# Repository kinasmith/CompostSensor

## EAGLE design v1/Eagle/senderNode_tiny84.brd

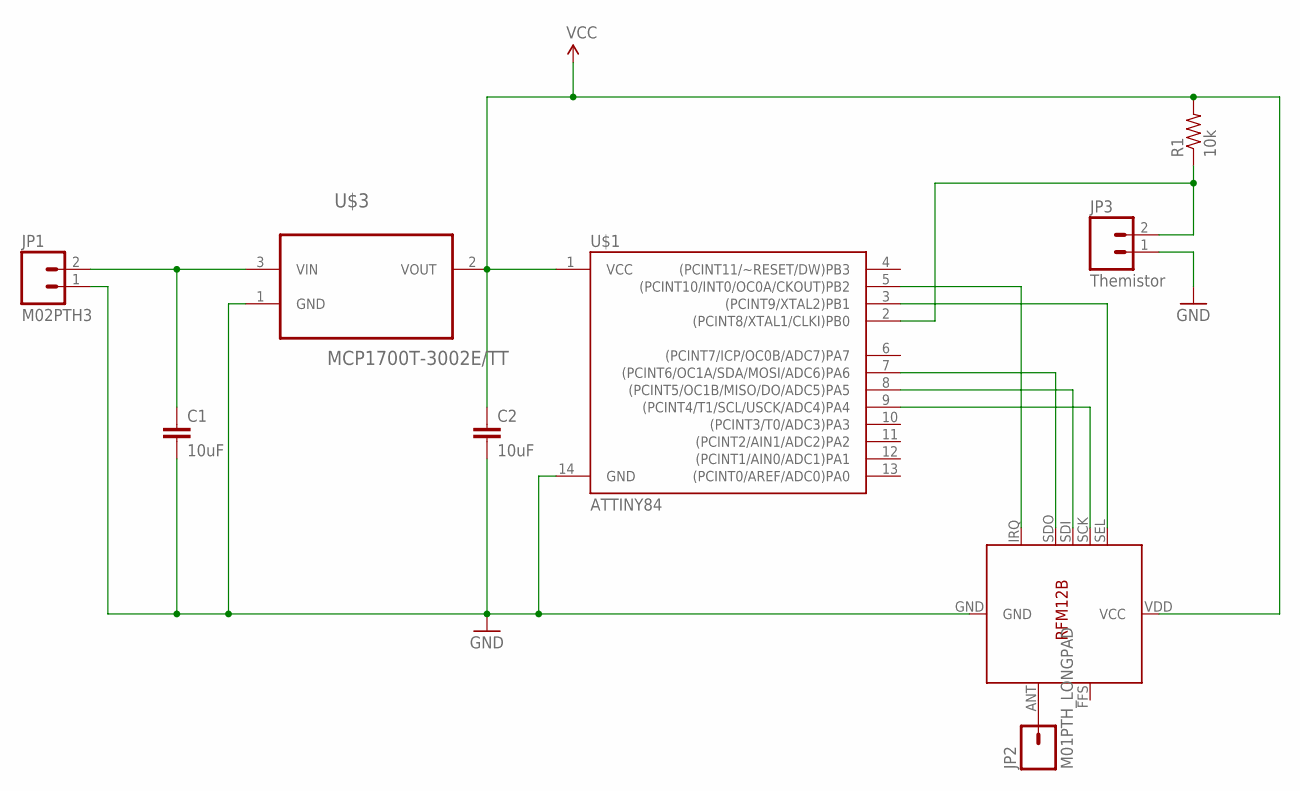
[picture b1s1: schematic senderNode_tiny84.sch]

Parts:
C1, C2: 10uF; 0603-CAP
JP1: M02PTH3; 1X02_LONGPADS
JP2: M01PTH_LONGPAD; 1X01_LONGPAD
JP3: Themistor; 1X02_LONGPADS
R1: 10k; 0805
U$1: ATTINY84; SO14
U$2: RFM12B
U$3: MCP1700T-3002E/TT; SOT95P237X112-3N

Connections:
GND: C1.2, C2.2, JP1.1, JP3.1, U$1.14 (GND), U$2.GND, U$3.1 (GND)
unnamed: U$1.5 ((PCINT10/INT0/OC0A/CKOUT)PB2), U$2.IRQ
unnamed: U$1.7 ((PCINT6/OC1A/SDA/MOSI/ADC6)PA6), U$2.SDO
unnamed: U$1.8 ((PCINT5/OC1B/MISO/DO/ADC5)PA5), U$2.SDI
unnamed: U$1.9 ((PCINT4/T1/SCL/USCK/ADC4)PA4), U$2.SCK
unnamed: U$1.3 ((PCINT9/XTAL2)PB1), U$2.SEL
unnamed: C1.1, JP1.2, U$3.3 (VIN)
unnamed: JP3.2, R1.1, U$1.2 ((PCINT8/XTAL1/CLKI)PB0)
unnamed: JP2.1, U$2.ANT
VCC: C2.1, R1.2, U$1.1 (VCC), U$2.VDD (VCC), U$3.2 (VOUT)

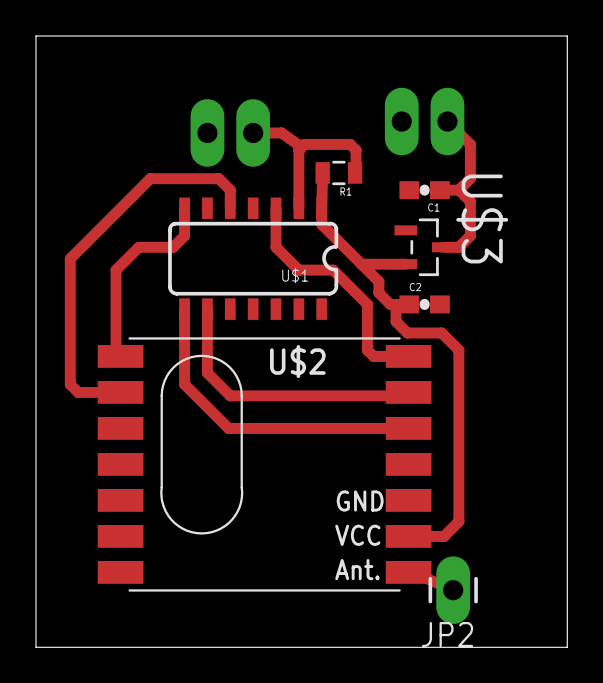
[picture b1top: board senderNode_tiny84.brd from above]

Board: 2 copper layers, 29.5 x 34.0 mm, 9 parts (0 on the bottom side), 10 nets.

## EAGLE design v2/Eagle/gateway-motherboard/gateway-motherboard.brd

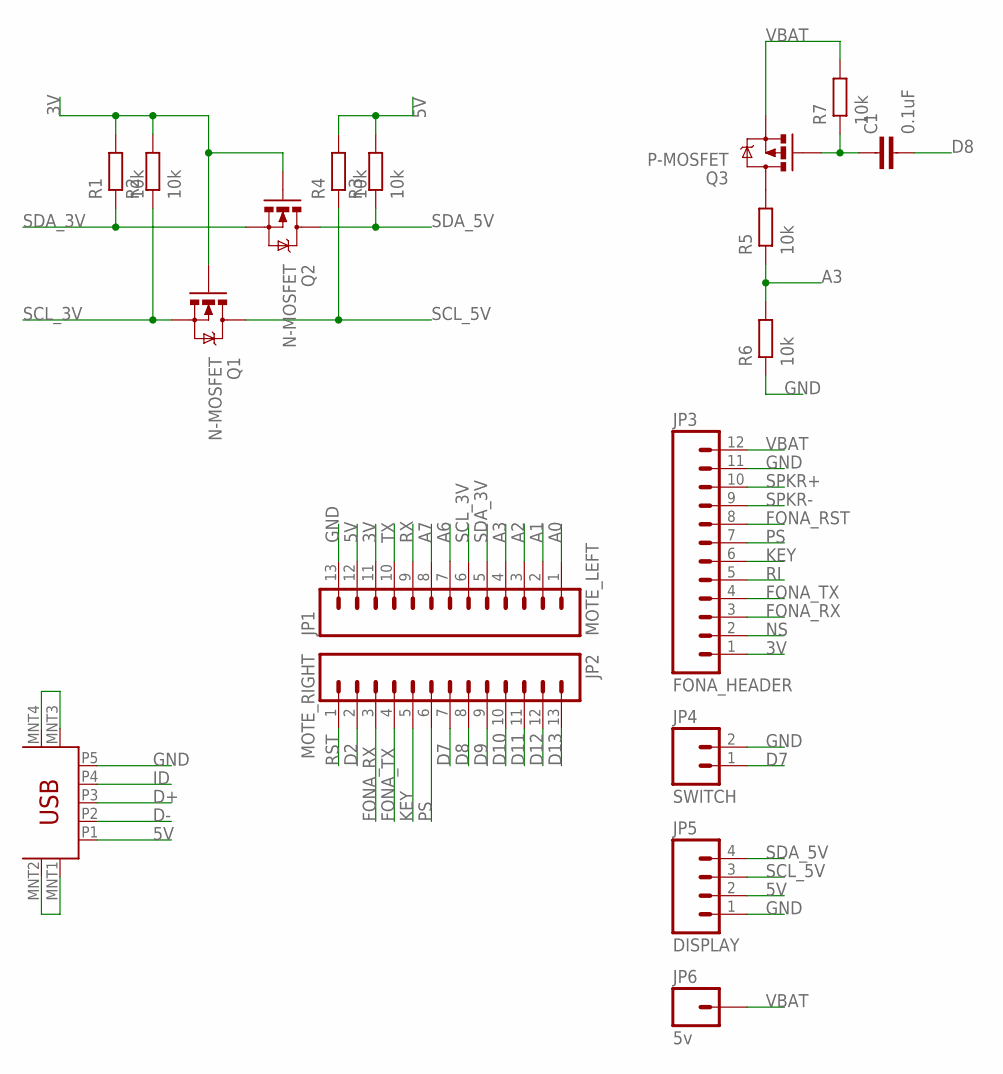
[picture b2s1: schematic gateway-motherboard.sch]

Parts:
C1: 0.1uF; C0603-L
JP1: MOTE_LEFT; 1X13-LONGPADS
JP2: MOTE_RIGHT; 1X13-LONGPADS
JP3: FONA_HEADER; 1X12_LONGPADS
JP4: SWITCH; 1X02_LOCK_LONGPADS
JP5: DISPLAY; 1X04_LONGPADS
JP6: 5v; 1X01NS-KIT
Q1, Q2: N-MOSFET; SOT23
Q3: P-MOSFET; SOT23-3
R1, R2, R3, R4, R5, R6, R7: 10k; R0603-L
U$1: USB-MINIB; USB-MINIB_HOLE_RETENTION

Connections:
3V: JP1.11, JP3.1, Q1.1 (G), Q2.1 (G), R1.2, R2.2
5V: JP1.12, JP5.2, R3.2, R4.2, U$1.P1 (VBUS)
A0: JP1.1
A1: JP1.2
A2: JP1.3
A3: JP1.4, R5.1, R6.2
A6: JP1.7
A7: JP1.8
D2: JP2.2
D7: JP2.7, JP4.1
D8: C1.2, JP2.8
D9: JP2.9
D10: JP2.10
D11: JP2.11
D12: JP2.12
D13: JP2.13
D+: U$1.P3 (D+)
D-: U$1.P2 (D-)
FONA_RST: JP3.8
FONA_RX: JP2.3, JP3.3
FONA_TX: JP2.4, JP3.4
GND: JP1.13, JP3.11, JP4.2, JP5.1, R6.1, U$1.MNT1 (MTN1), U$1.MNT2 (MTN2), U$1.MNT3 (MTN3), U$1.MNT4 (MTN4), U$1.P5 (GND)
ID: U$1.P4 (ID)
KEY: JP2.5, JP3.6
unnamed: Q3.3 (D), R5.2
unnamed: C1.1, Q3.1 (G), R7.1
NS: JP3.2
PS: JP2.6, JP3.7
RI: JP3.5
RST: JP2.1
RX: JP1.9
SCL_3V: JP1.6, Q1.2 (S), R2.1
SCL_5V: JP5.3, Q1.3 (D), R4.1
SDA_3V: JP1.5, Q2.2 (S), R1.1
SDA_5V: JP5.4, Q2.3 (D), R3.1
SPKR+: JP3.10
SPKR-: JP3.9
TX: JP1.10
VBAT: JP3.12, JP6.1, Q3.2 (S), R7.2

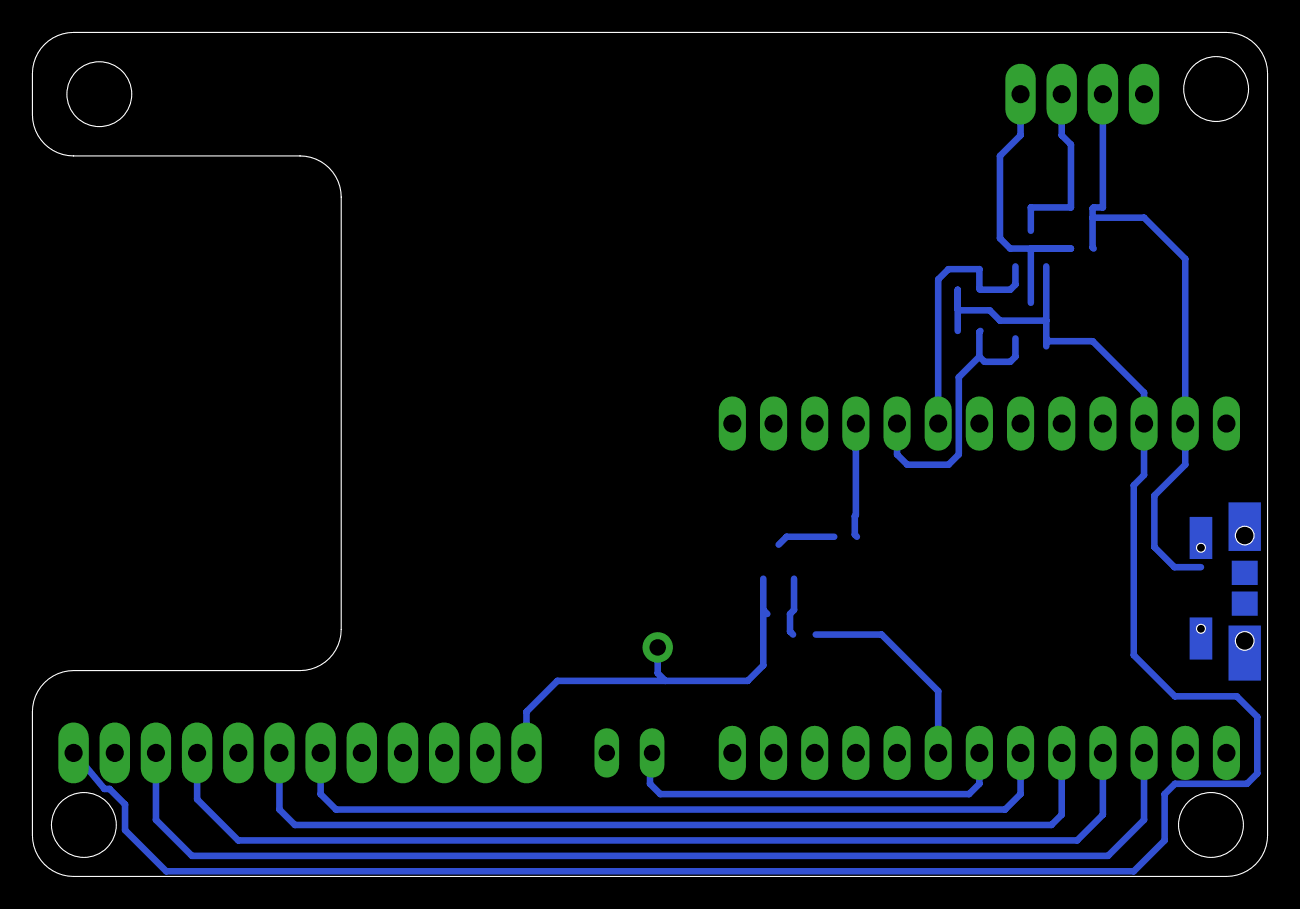
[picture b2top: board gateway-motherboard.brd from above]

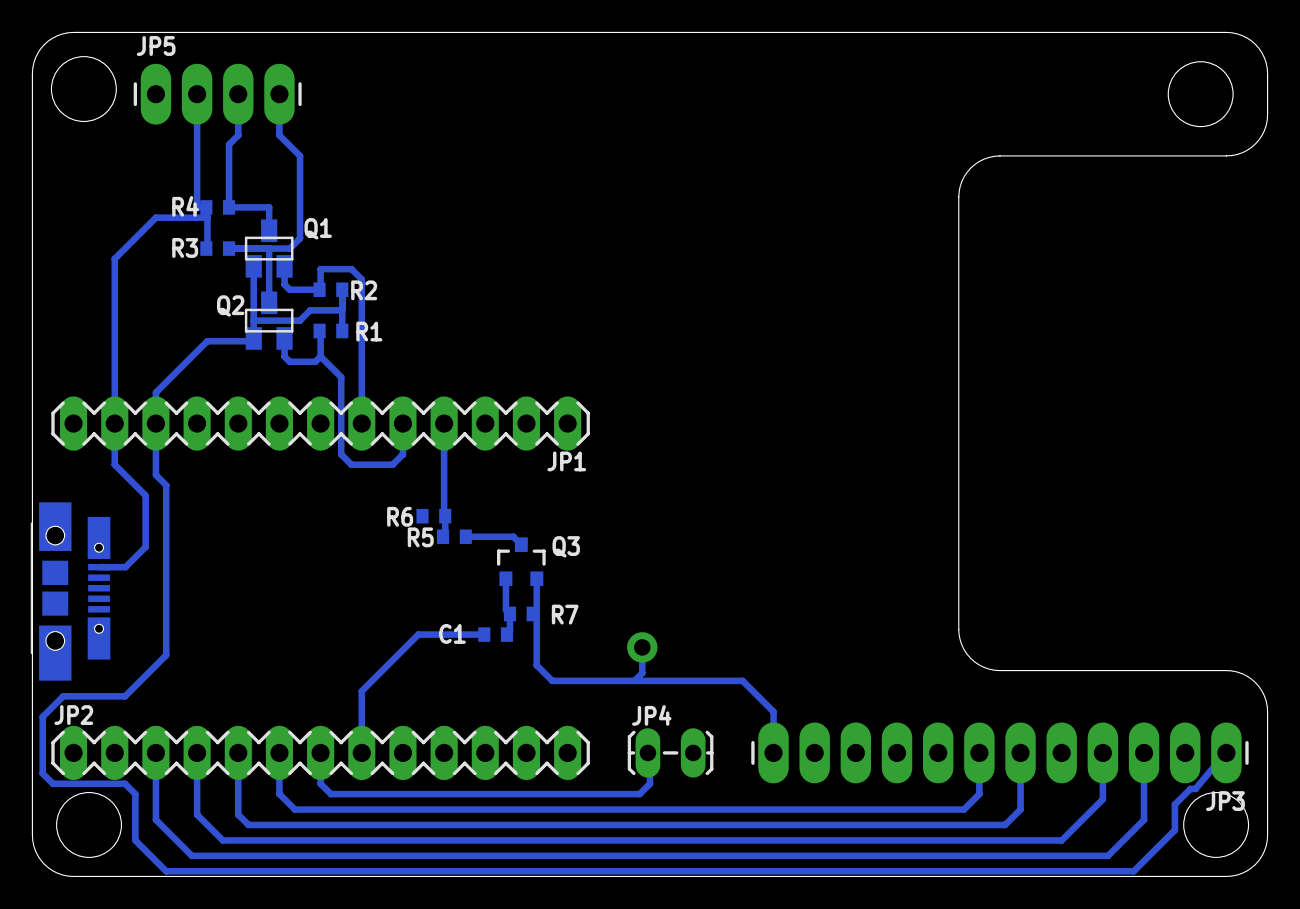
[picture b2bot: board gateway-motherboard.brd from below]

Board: 2 copper layers, 76.2 x 52.1 mm, 18 parts (18 on the bottom side), 17 nets.

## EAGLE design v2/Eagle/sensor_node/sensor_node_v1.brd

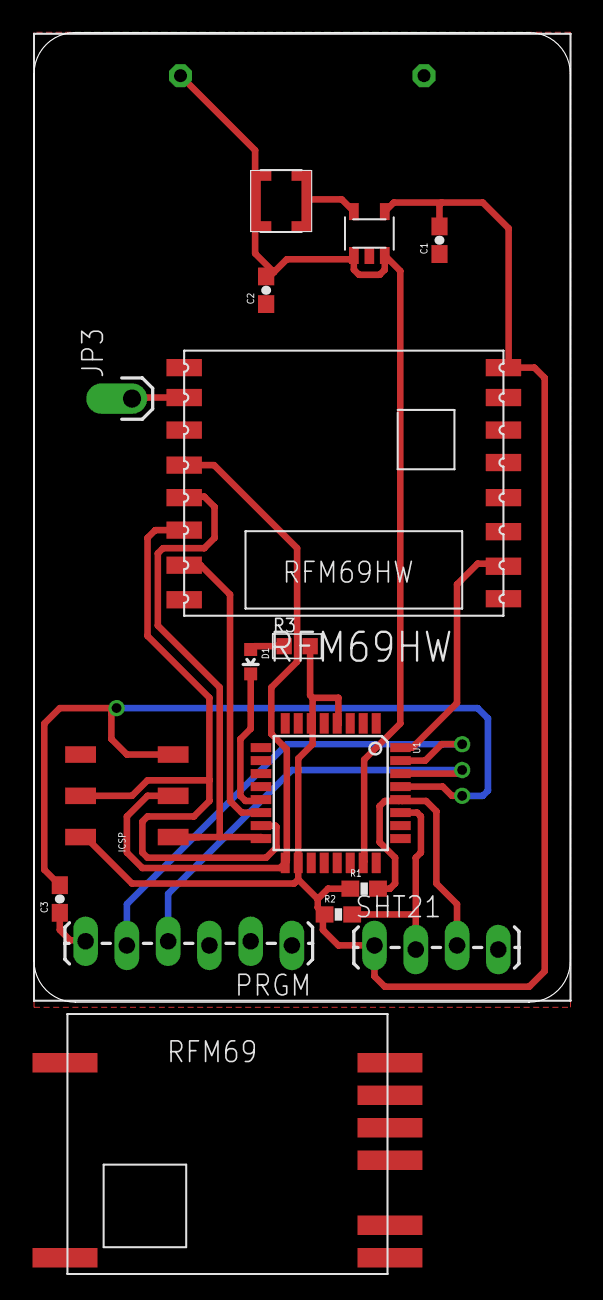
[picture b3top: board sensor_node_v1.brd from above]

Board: 2 copper layers, 33.0 x 59.7 mm, 17 parts (0 on the bottom side), 18 nets.

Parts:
C1, C2: 10uF; 0603-CAP
C3: 0.1uF; 0603-CAP
D1: BLUE; LED-0603
ICSP: 2X3_SMD
JP3: M01OFFSET; 1X01_OFFSET
PRGM: 1X06_LOCK_LONGPADS
R1, R2: 10k; 0603-RES
R3: R0603-N
RFM69HW: RFM69HW; RFM
SHT21: 1X04_LOCK_LONGPADS
U1: ATMEGA328P; TQFP32-08
U$1: KEYSTONEAAHOLDER_2CELL
U$2: TPS61097-33; SOT23-5
U$3: COILCRAFT_DO3314
U$4: RFM69HW_MIN; RFM69

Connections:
ANT: JP3.1, RFM69HW.ANT
GND: C1.1, C2.1, ICSP.6, PRGM.1, RFM69HW.GNDB, SHT21.4, U1.3, U1.5, U1.21, U$1.P$2, U$2.P$2
IRQ: RFM69HW.DIO0, U1.32
LED: D1.C, U1.13
MISO: ICSP.1, RFM69HW.MISO, U1.16
MOSI: ICSP.4, RFM69HW.MOSI, U1.15
unnamed: U$2.P$5, U$3.P$1
unnamed: C3.1, PRGM.6
unnamed: D1.A, R3.1
RST: C3.2, ICSP.5, U1.29
RX: PRGM.4, U1.30
SCK: ICSP.3, RFM69HW.SCK, U1.17
SCL: R1.2, SHT21.3, U1.28
SDA: R2.2, SHT21.2, U1.27
SS: RFM69HW.NSS, U1.14
TX: PRGM.5, U1.31
VBAT: C2.2, U1.23, U$1.P$1, U$2.P$1, U$2.P$3, U$3.P$2
VCC: C1.2, ICSP.2, R1.1, R2.1, R3.2, RFM69HW.VCC, SHT21.1, U1.4, U1.6, U1.18, U$2.P$4

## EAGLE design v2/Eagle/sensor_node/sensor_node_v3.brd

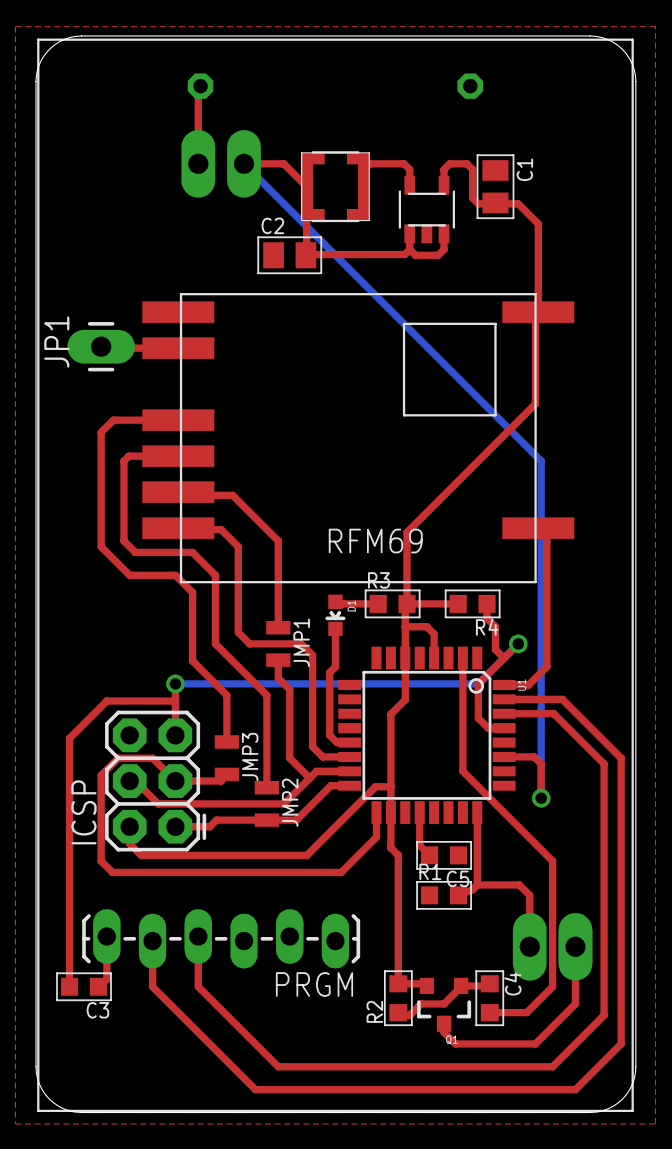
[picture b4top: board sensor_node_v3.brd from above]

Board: 2 copper layers, 33.3 x 59.8 mm, 24 parts (0 on the bottom side), 25 nets.

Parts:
C1, C2: 10uF; C0805-N
C3, C4, C5: 0.1uF; C0603-N
D1: BLUE; LED-0603
ICSP: 2X3
JMP1, JMP2: 0; R0805-L
JMP3: o; R0805-L
JP1: M01PTH_LONGPAD; 1X01_LONGPAD
JP2: THERM; 1X02_LONGPADS
JP3: PWR_SW; 1X02_LONGPADS
PRGM: 1X06_LOCK_LONGPADS
Q1: MOSFET-PCHANNELSMD; SOT23-3
R1, R2, R4: 10k; R0603-N
R3: R0603-N
U1: ATMEGA328P; TQFP32-08
U$1: KEYSTONEAAHOLDER_2CELL
U$2: TPS61097-33; SOT23-5
U$3: COILCRAFT_DO3314
U$4: RFM69HW_MIN; RFM69

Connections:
ANT: JP1.1, U$4.ANA
GND: C1.1, C2.1, C5.1, ICSP.6, PRGM.1, R1.1, U1.3, U1.5, U1.21, U$1.P$2, U$2.P$2, U$4.GND
IRQ: U1.32, U$4.DIO0
LED: D1.C, U1.13
MISO: ICSP.1, JMP2.2, U1.16
MOSI: ICSP.4, JMP1.2, U1.15
unnamed: U$2.P$5, U$3.P$1
unnamed: C3.1, PRGM.6
unnamed: D1.A, R3.1
unnamed: JMP1.1, U$4.MOSI
unnamed: JMP2.1, U$4.MISO
unnamed: JMP3.1, U$4.SCK
unnamed: JP3.1, U$1.P$1
unnamed: C4.1, Q1.1, R2.1
unnamed: C5.2, U1.20
unnamed: JP2.2, Q1.3
RST: C3.2, ICSP.5, R4.1, U1.29
RX: PRGM.4, U1.30
SCK: ICSP.3, JMP3.2, U1.17
SS: U1.14, U$4.NSS
THERM: JP2.1, R1.2, U1.24
THERM_EN: C4.2, U1.2
TX: PRGM.5, U1.31
VBAT: C2.2, JP3.2, U1.27, U$2.P$1, U$2.P$3, U$3.P$2
VCC: C1.2, ICSP.2, Q1.2, R2.2, R3.2, R4.2, U1.4, U1.6, U1.18, U$2.P$4, U$4.VCC

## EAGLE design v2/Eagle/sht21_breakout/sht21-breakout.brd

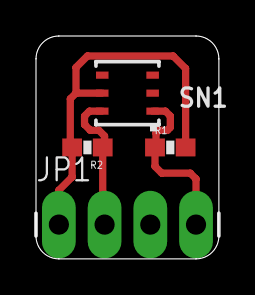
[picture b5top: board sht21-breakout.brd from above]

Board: 2 copper layers, 10.2 x 12.4 mm, 4 parts (0 on the bottom side), 4 nets.

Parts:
JP1: 1X04_LONGPADS
R1, R2: 10k; 0603-RES
SN1: SHT21; DFN6/SHT

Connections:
GND: JP1.3, SN1.2
SCL: JP1.2, R2.1, SN1.6
SDA: JP1.4, R1.1, SN1.1
VCC: JP1.1, R1.2, R2.2, SN1.5

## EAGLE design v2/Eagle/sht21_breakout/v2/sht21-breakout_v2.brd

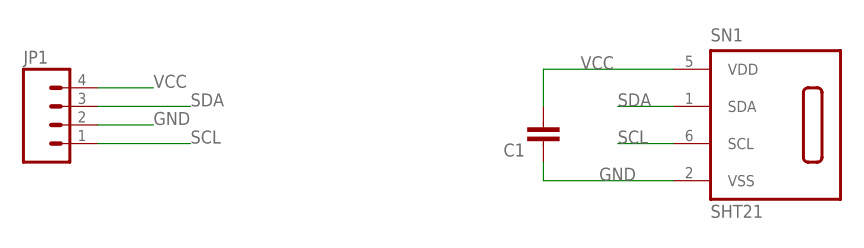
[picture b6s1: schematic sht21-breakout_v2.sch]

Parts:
C1: CAPACITOR0603-N; C0603-N
JP1: M04LONGPADS; 1X04_LONGPADS
SN1: SHT21; DFN6/SHT

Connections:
GND: C1.1, JP1.2, SN1.2 (VSS)
SCL: JP1.1, SN1.6 (SCL)
SDA: JP1.3, SN1.1 (SDA)
VCC: C1.2, JP1.4, SN1.5 (VDD)

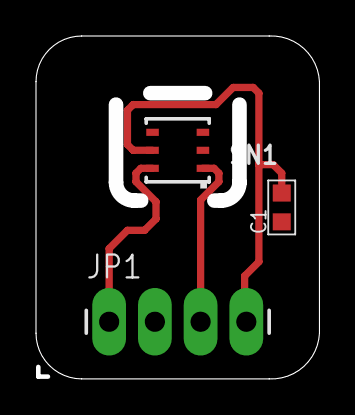
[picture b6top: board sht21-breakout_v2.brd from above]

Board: 2 copper layers, 15.7 x 19.1 mm, 3 parts (0 on the bottom side), 4 nets.

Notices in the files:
parts and their libraries:
SparkFun-Resistors: Licensing: CC v3.0 Share-Alike You are welcome to use this library for commercial purposes.
sensirion: Copyright (C) 2011, Bob Starr
